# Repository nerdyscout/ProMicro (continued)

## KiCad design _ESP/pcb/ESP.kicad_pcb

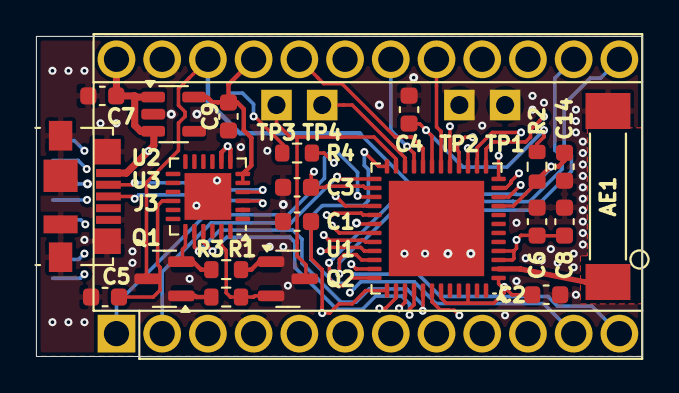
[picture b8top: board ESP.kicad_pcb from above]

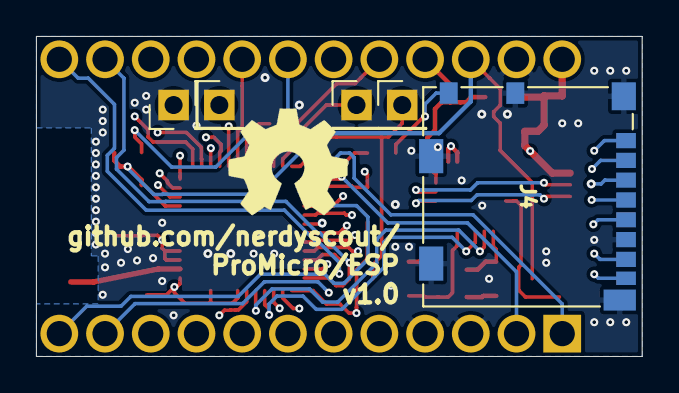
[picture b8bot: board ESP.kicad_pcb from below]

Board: 4 copper layers, 33.7 x 17.8 mm, 28 parts (6 on the bottom side), 44 nets.

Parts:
A1: Sparkfun_Pro_Micro; ProMicro
AE1: Antenna_Chip; SMD_ANT9520
C1, C2, C7, C14: 1µ; C_0603_1608Metric
C3, C9: 0.1n; C_0603_1608Metric
C4, C6: 100n; C_0603_1608Metric
C5: DNP; C_0603_1608Metric
C8: 10n; C_0603_1608Metric
J3: USB_B_Micro; USB_Micro-B_Molex_47346-0001
J4: Micro_SD_Card_Det; microSD_HC_Molex_104031-0811
LOGO1: Logo_Open_Hardware_Small; OSHW-Symbol_6.7x6mm_SilkScreen
Q1, Q2: mmbt2222; SOT-23
R1, R2, R3, R4: 10k; R_0603_1608Metric
TP1: GPIO21; PinHeader_1x01_P2.54mm_Vertical
TP2: GPIO22; PinHeader_1x01_P2.54mm_Vertical
TP3: GPIO0; PinHeader_1x01_P2.54mm_Vertical
TP4: GPIO2; PinHeader_1x01_P2.54mm_Vertical
U1: ESP32-PICO-D4; QFN-48-1EP_7x7mm_P0.5mm_EP5.3x5.3mm
U2: AP2112K-3.3; SOT-23-5
U3: CP2104; QFN-24-1EP_4x4mm_P0.5mm_EP2.6x2.6mm

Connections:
+3V3: A1.21, C1.1, C2.1, C4.1, C6.1, C8.1, C9.1, R2.1, U1.1, U1.3, U1.4, U1.19, U1.37, U1.43, U1.46, U2.5, U3.5, U3.6
+5V: A1.24, C7.1, J3.1, U2.1, U2.3, U3.7, U3.8
/CLK: J4.5, U1.31
/CMD: J4.3, U1.30
/D0: J4.7, U1.32
/D1: J4.8, U1.33
/D2: J4.1, U1.28
/D3: J4.2, U1.29
/D+: J3.3, U3.3
/D-: J3.2, U3.4
/DTR: Q2.2, R1.2, U3.23
/GPIO0: Q2.3, TP3.1, U1.23
/GPIO2: TP4.1, U1.22
/RTS: Q1.2, R3.2, U3.19
/VDDSDIO: C3.1, J4.4, U1.26
BTN: A1.9, R4.1, U1.14
CIPO: A1.15, U1.38
COPI: A1.14, U1.36
CS0: A1.13, U1.34
CS1: A1.12, U1.24
D8: A1.11, U1.16
GND: A1.3, A1.4, A1.23, AE1.2, C1.2, C2.2, C3.2, C4.2, C5.2, C6.2, C7.2, C8.2, C9.2, C14.2, J3.5, J3.6, J4.6, J4.9, J4.11, U1.49, U2.2, U3.2, U3.25
INT: A1.10, U1.13
unnamed: AE1.1, U1.2
unnamed: C5.1, U3.16
unnamed: J4.10, R4.2
unnamed: Q1.1, R1.1
unnamed: Q2.1, R3.1
unnamed: TP1.1, U1.42
unnamed: TP2.1, U1.39
PWM: A1.8, U1.12
RXD: U1.40, U3.21
RXD2: A1.2, U1.25
SCK: A1.16, U1.35
SCL: A1.6, U1.10
SDA: A1.5, U1.11
STAT: A1.7, U1.15
TCK: A1.20, U1.20
TDI: A1.17, U1.18
TDO: A1.18, U1.21
TMS: A1.19, U1.17
TXD: U1.41, U3.20
TXD2: A1.1, U1.27
~RST: A1.22, C14.1, Q1.3, R2.2, U1.9

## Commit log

2020-02-22 init
2020-02-22 moved schematic, update links
2020-02-22 auto generated by github actions
2020-02-22 relative pathes
2020-02-22 fixed path
2020-02-23 schematic, placed parts
2020-02-23 svg2gerber
2020-02-23 init kicost
2020-02-24 final draft
2020-02-26 added solder pads for opposite PCB antenna connector
2020-03-01 moved text a bit
2020-03-05 ProMicro running GPS
2020-03-05 seperate cleanup
2020-03-05 final
2020-03-05 update by github actions
2020-03-05 ProMicro does have two hardware serial, no software nedded
2020-03-05 fixed both examples
2020-03-05 added jumper for TX and RX
2020-03-05 single line pictures
2020-03-06 renamed files
2020-03-07 fully routed
2020-03-07 rotated breakout pins
2020-03-13 Add changes
2020-03-13 new docs
2020-03-14 new docu
2020-03-14 fixes
2020-03-14 moved labels from fab to silk
2020-03-14 moved files
2020-03-14 hole diamter
2020-03-14 pin docu and wider holes
2020-03-14 improved docu
2020-03-14 added pictures
2020-03-14 docu in layout
2020-03-15 a lot of docu
2020-03-15 docu
2020-03-15 rename project
2020-03-15 add debug
2020-03-15 comment out bom.csv which is not created for some reason
2020-03-15 update description
2020-03-15 absolut path
2020-03-17 variant management
2020-03-17 add mouting brackets
2020-03-17 fixed docu
2020-03-17 add EdgeCuts to layer svg
2020-03-17 fixed img link
2020-03-24 better ci
2020-03-24 replacements by Github Actions
2020-03-24 update ci
2020-03-24 rm update ci
2020-03-25 add update CI
2020-03-25 add mounting brackets
2020-03-25 upgrade PCB layout
2020-07-06 trigger CI run
2020-07-06 fabrications
2020-07-06 docs
2020-07-06 update tracespace
2020-07-06 upgrade
2020-07-10 add 5v signal
2020-07-11 update workflow
2020-07-11 test
2020-07-20 warning
2020-07-28 changed SPI signal names
2020-08-02 trigger workflow run
2020-08-03 test develop kicad-exports
2020-08-03 trigger rerun
2020-08-07 test conig.kiplot.yaml
2020-08-07 update autogenerated files
2020-08-14 kicad-exports
2020-08-14 running kicad-exports
2020-08-14 kicad-exports@v2.0
2020-08-15 fixed missing TRG
2020-08-15 add pcbs
2020-08-21 buffer stil need fixes
2020-09-04 move file to merge
2020-09-04 clean repo
2020-09-04 major cleanup and merge of all PCBs
2020-09-04 cleaning some files
2020-09-05 add 1.8V for Gyro
2020-09-05 test branchname
2020-09-05 adding holes for antenna
2020-09-06 changed signal names
2020-09-06 fixing filter
2020-09-06 new relative controller schematic
2020-09-06 removed relative controller again as it would mean double page schematics
2020-09-06 update GPS
2020-10-18 dump
2020-10-31 clean
2020-10-31 route
2020-10-31 v3.0
2020-11-16 auto tag current branch with version
2020-11-18 update update script
2020-11-19 update schematic and PCBs
2020-11-19 update kicad-exports config
2020-11-19 add discord
2020-11-19 project update
2020-11-19 run always
2020-11-19 try almighty config
2020-11-19 fix ERC/DRC and add power planes
2020-11-21 make controller holes wide enough
2020-11-21 update PCBs to be stackable
2020-11-21 cleanup
2020-11-21 update kibot config
2020-11-21 update PCBS
2020-11-22 update links to files
2020-11-22 update design
2020-11-22 rm space
2020-11-22 change local symbol lib
2020-11-22 fixed lib
2020-11-22 merged libs into one
2020-11-22 un/hide layers
2020-11-22 using some default values
2020-11-22 do not delete local project config
2020-11-22 update all readme to their files
2020-11-22 always force adding tags
2020-12-01 rm discord server
2021-01-23 clean ESP projects
2021-02-27 LORA_v1.3
2021-03-07 BOOST_v1.8
2021-03-12 made all SMD parts 0603
2021-03-17 BOOST
2021-03-17 LORA
2021-03-17 ADAPT
2021-03-17 CONN
2021-03-17 UART
2021-03-17 SAMD
2021-03-17 QWIIC
2021-03-17 WING
2021-03-17 stuff
2021-04-05 fixed workflow
2021-04-05 trigger workflow
2021-04-05 run kicad-exports v2.3
2021-04-05 update schematic date
2021-04-05 update board date
2021-04-08 run always on latest develop
2021-04-18 use new kibot.lst bundle
2021-04-18 Apply automatic changes
2021-04-18 enabled to run only on schematic/board changes
2021-04-18 add cad/* files to all projects
2021-04-18 update project files
2021-04-19 fixed readme
2021-04-19 update all project files
2021-04-20 changed VCC of CP2104
2021-08-30 blindly dumped everything
2021-10-24 moved documentation text
2021-10-24 fix some ERC/DRC
2021-10-25 major cleanup and fixes
2024-12-26 update links
2024-12-27 cleanup using licenses
2025-01-05 add dev container
2025-01-05 update license
2025-01-06 fix: ignore devcontainer from reuse
2025-01-06 add variant kibot config
2025-01-06 disable stackup update
2025-01-06 add whitespaces in table
2025-01-06 renamed readme
